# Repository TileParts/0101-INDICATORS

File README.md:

0101-INDICATORS
==========

一块 LED 灯板。

## 特性

1. 低电平有效，需要连接 3.3V 为 LED 供电
2. 双排针并联，方便将信号继续转接到别的地方，如逻辑分析仪
3. 排针与 LED 之间可覆盖美纹纸自行标记
4. 背面预留 ESD 器件的焊盘（需要连接 GND）

## 协议

[CERN-OHL-P-2.0](LICENSE)

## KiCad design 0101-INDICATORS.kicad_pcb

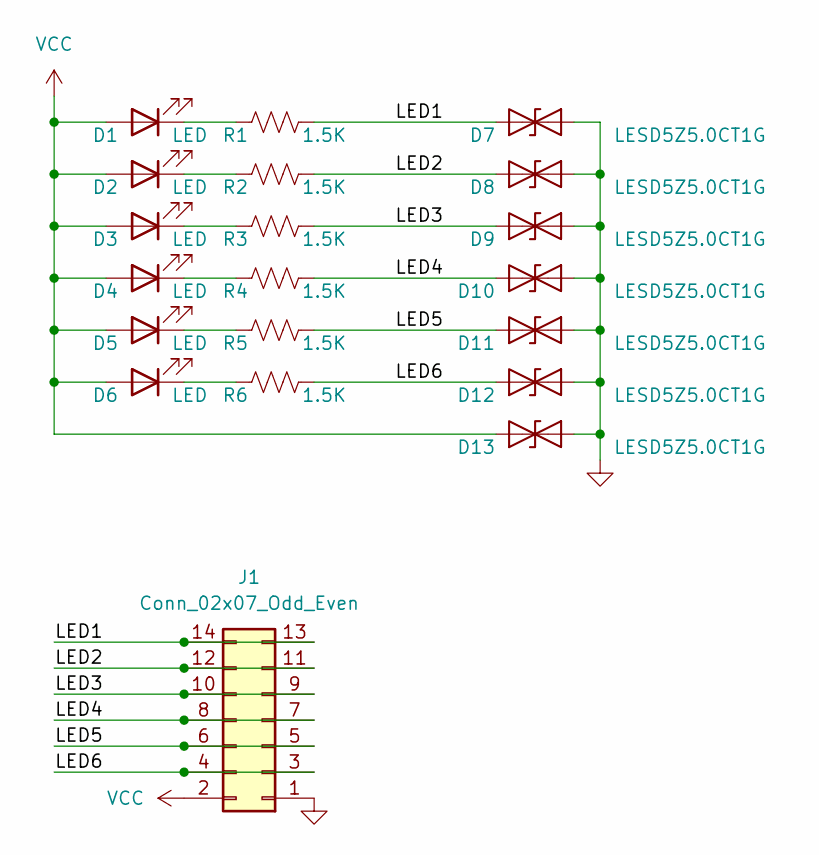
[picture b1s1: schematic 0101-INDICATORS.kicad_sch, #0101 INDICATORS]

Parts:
D1, D2, D3, D4, D5, D6: LED; LED_0603_1608Metric; PartNumber C72041
D7, D8, D9, D10, D11, D12, D13: LESD5Z5.0CT1G; D_SOD-523; PartNumber C136167
J1: Conn_02x07_Odd_Even; PinHeader_2x07_P2.54mm_Vertical
R1, R2, R3, R4, R5, R6: 1.5K; R_0402_1005Metric; PartNumber C25867

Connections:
/LED1: D7.1 (A1), J1.13, J1.14, R1.2
/LED2: D8.1 (A1), J1.11, J1.12, R2.2
/LED3: D9.1 (A1), J1.9, J1.10, R3.2
/LED4: D10.1 (A1), J1.7, J1.8, R4.2
/LED5: D11.1 (A1), J1.5, J1.6, R5.2
/LED6: D12.1 (A1), J1.3, J1.4, R6.2
GND: D7.2 (A2), D8.2 (A2), D9.2 (A2), D10.2 (A2), D11.2 (A2), D12.2 (A2), D13.2 (A2), J1.1
unnamed: D1.1 (K), R1.1
unnamed: D2.1 (K), R2.1
unnamed: D3.1 (K), R3.1
unnamed: D4.1 (K), R4.1
unnamed: D5.1 (K), R5.1
unnamed: D6.1 (K), R6.1
VCC: D1.2 (A), D2.2 (A), D3.2 (A), D4.2 (A), D5.2 (A), D6.2 (A), D13.1 (A1), J1.2

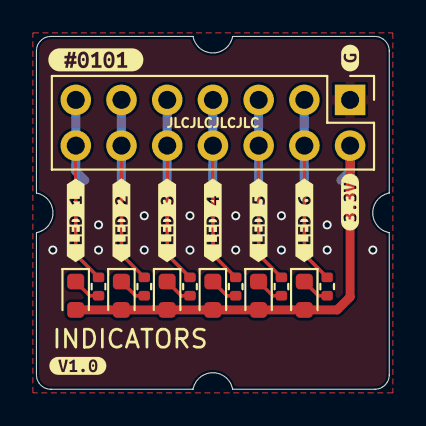
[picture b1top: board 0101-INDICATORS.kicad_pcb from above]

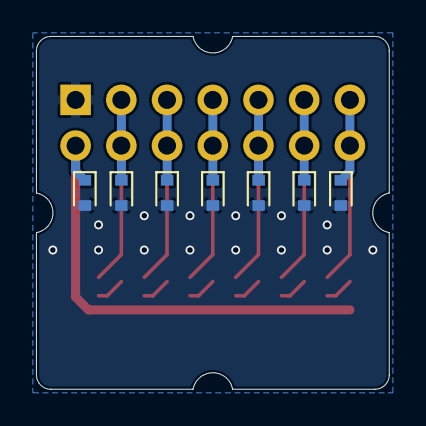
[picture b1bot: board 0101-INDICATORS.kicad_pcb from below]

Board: 2 copper layers, 19.6 x 19.6 mm, 30 parts (7 on the bottom side), 14 nets.

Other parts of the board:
kibuzzard-633FDF9B: G***; kibuzzard-633FDF9B
kibuzzard-633FDF9F: G***; kibuzzard-633FDF9F
kibuzzard-633FDF52: G***; kibuzzard-633FDF52
kibuzzard-633FDFA3: G***; kibuzzard-633FDFA3
kibuzzard-633FDFA7: G***; kibuzzard-633FDFA7
kibuzzard-633FDFAC: G***; kibuzzard-633FDFAC
kibuzzard-633FE25F: G***; kibuzzard-633FE25F
kibuzzard-633FE26A: G***; kibuzzard-633FE26A
kibuzzard-63351A8A: G***; kibuzzard-63351A8A
kibuzzard-63351A9D: G***; kibuzzard-63351A9D

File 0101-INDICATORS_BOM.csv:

Manufacturer,Comment,Designator,Footprint,Quantity,PartNumber,Supplier
EVERLIGHT,LED,D1 D2 D3 D4 D5 D6,LED_0603_1608Metric,6,C72041,JLC
UniOhm,1.5K,R1 R2 R3 R4 R5 R6,R_0402_1005Metric,6,C25867,JLC
LRC,LESD5Z5.0CT1G,D7 D8 D9 D10 D11 D12 D13,D_SOD-523,7,C136167,JLC-EXT

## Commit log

2022-10-07 Init repo
2022-10-07 Make indicators
2022-10-07 Fix 3d model
2022-10-07 Output docs
2022-10-07 Add README
2022-10-07 Output SCH
